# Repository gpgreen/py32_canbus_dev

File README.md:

# py32_canbus_dev

KiCad design for a ARM Cortex-M0+ CAN bus development board with a
MCP2518 CAN FD controller. The mcu part is a Puya PY032F030K18T6. This
can run at a maximum of 48 MHz, and has 8 kbyte SRAM and 64 kbyte
Flash. A USB B mini connector provides 5V power and interfaces with a
FTDI device wired as a Serial Comm to the development board. There is
an onboard LDO that provides 500mA of power at 3.3V. An LED is
connected to 1 of the GPIO pins. All available GPIO pins are routed to
the 2 18pin headers.

The board must be programmed with a debugger, ie at this time it
cannot be programmed over the usb.

## Changes

- Rev A
  Original

## Firmware

Example firmware that blinks the LED. This firmware
uses the HAL provided by Puya and is in C.

https://github.com/gpgreen/py32-dev-blink

## Boot configuration

A boot configuration must be selected for the development board to
operate. If a program has been flashed then booting from main flash
should be selected for that program to run.

To boot from main flash [0x0800_0000] Connect J2-4 to J2-5 (or) solder
  JP5-1 to center post

To boot from System mem [0x1FFF_0000], or Embedded SRAM [0x2000_0000]
  Connect J2-4 to J2-3 (or) solder JP6-3 to center post

There is an embedded boot loader, programmed during mcu chip
production, in the system memory block. See the reference manual
3.6.2.

## PIN JUMPER SIGNAL ASSIGNMENT
```
                     USB-B
                    +-----+
            +--------------------+
            |J3     |     |    J2|
        VDD-|1      +-----+     1|-GND
        GND-|2                  2|-GND
       +3.3-|3                  3|-+3.3
[RESET] PF2-|4                  4|-PF4 [BOOT0_PRE]
[SWCLK]PA14-|5                  5|-GND
[SWDIO]PA13-|6                  6|-GND
        GND-|7       RST        7|-GND
        PF3-|8       +-+        8|-PB7 [USB RX]
        PA0-|9       |O|        9|-PB6 [USB TX]
  [SCK] PA1-|10      +-+       10|-PB5
 [MOSI] PA2-|11                11|-PB4
        PA3-|12                12|-PB3
  [NSS] PA4-|13                13|-PA15
[CAN I] PA5-|14                14|-PA12 [USER LED - GREEN]
 [MISO] PA6-|15                15|-PA11
        PA7-|16                16|-PA10
        PB0-|17                17|-PA9
        PB1-|18    +------+    18|-PA8
            |     1| o  o |2     |
            +--------------------+
                     H  L
                     CAN
```
## Links
- [Puya PY32 Series](https://www.puyasemi.com/cpzx3/info_271_aid_247_kid_246.html)
- [Software template for PY32 Series by Jay Carlson](https://github.com/jaydcarlson/py32-template)
- [Fork of template for these boards](https://github.com/gpgreen/py32-dev-blink)
- [Firmware library for py32f030](https://www.puyasemi.com/download_path/%E5%BA%93%E5%87%BD%E6%95%B0%E4%B8%8E%E4%BE%8B%E7%A8%8B/MCU/PY32F0xx_Firmware_V1.4.1.zip)

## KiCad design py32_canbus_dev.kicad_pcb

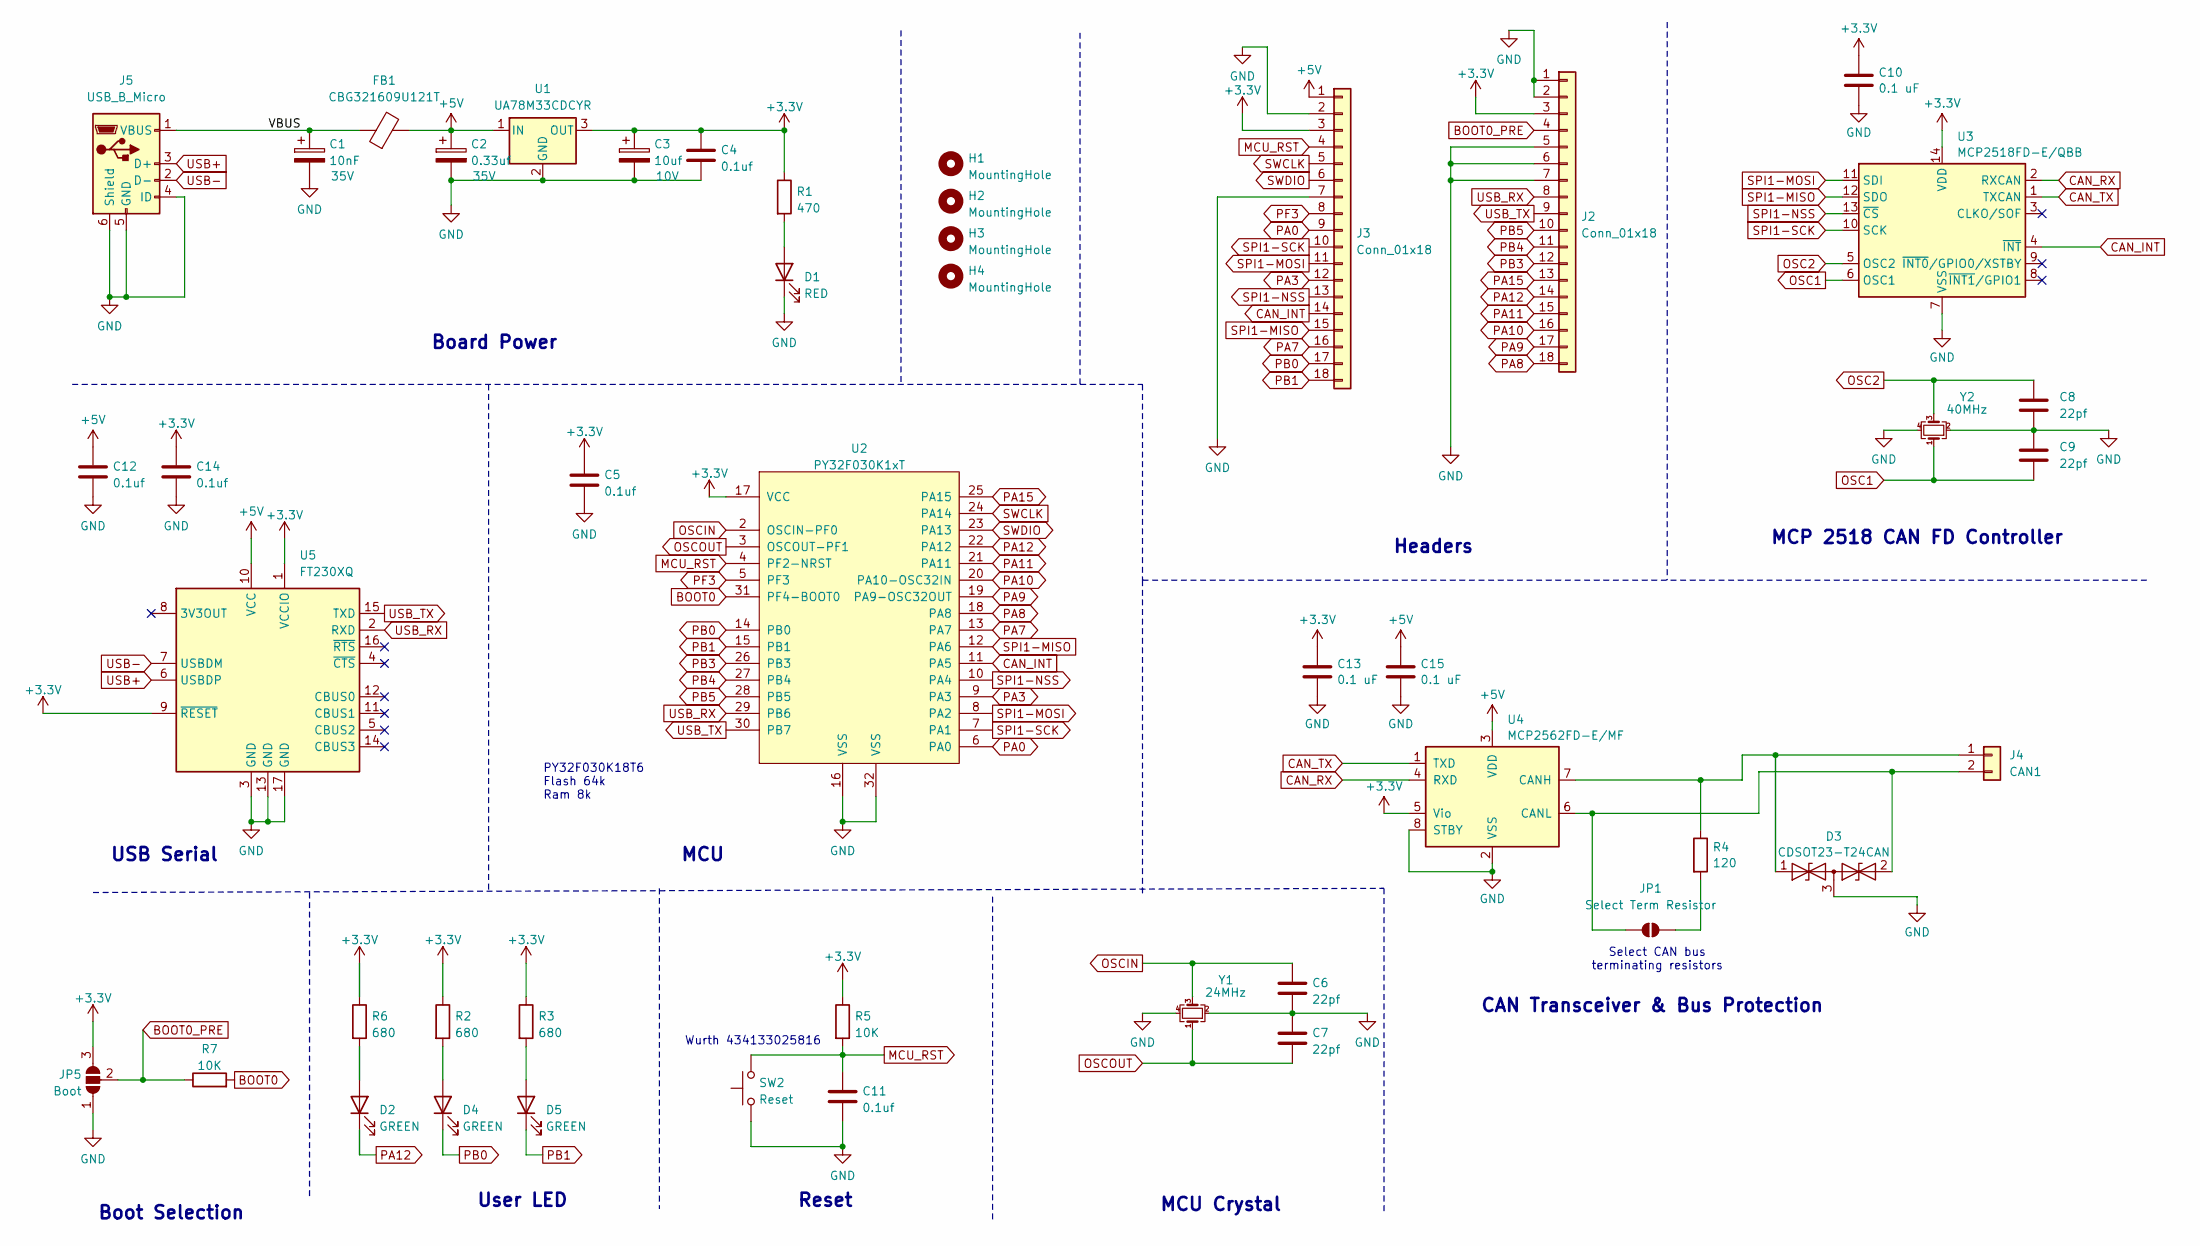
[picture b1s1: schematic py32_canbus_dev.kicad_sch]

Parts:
C1: 10nF; CP_EIA-3216-18_Kemet-A_Pad1.58x1.35mm_HandSolder; Voltage 35V
C2: 0.33uf; CP_EIA-3216-18_Kemet-A_Pad1.58x1.35mm_HandSolder; Voltage 35V
C3: 10uf; CP_EIA-3216-18_Kemet-A_Pad1.58x1.35mm_HandSolder; Voltage 10V
C4, C5, C11, C12, C14: 0.1uf; C_0603_1608Metric
C6, C7, C8, C9: 22pf; C_0603_1608Metric
C10, C13, C15: 0.1 uF; C_0603_1608Metric
D1: RED; D_0603_1608Metric
D2, D4, D5: GREEN; D_0603_1608Metric
D3: CDSOT23-T24CAN; SOT-23
FB1: CBG321609U121T; L_1206_3216Metric
H1, H2, H3, H4: MountingHole; MountingHole_3.2mm_M3
J2, J3: Conn_01x18; PinHeader_1x18_P2.54mm_Vertical
J4: CAN1; JST_EH_B2B-EH-A_1x02_P2.50mm_Vertical
J5: USB_B_Micro; USB_Micro-B_Amphenol_10103594-0001LF_Horizontal
JP1: Select Term Resistor; SolderJumper-2_P1.3mm_Open_Pad1.0x1.5mm
JP5: Boot; SolderJumper-3_P1.3mm_Open_Pad1.0x1.5mm_NumberLabels
R1: 470; R_0603_1608Metric
R2, R3, R6: 680; R_0603_1608Metric
R4: 120; R_1206_3216Metric
R5, R7: 10K; R_0603_1608Metric
SW2: Reset; SW_Push_1P1T_NO_Vertical_Wuerth_434133025816
U1: UA78M33CDCYR; SOT-223-3_TabPin2
U2: PY32F030K1xT; LQFP-32_7x7mm_P0.8mm
U3: MCP2518FD-E/QBB; DFN-14-1EP_3x4.5mm_P0.65mm_EP1.65x4.25mm
U4: MCP2562FD-E/MF; MICROCHIP-DFN-3x3x0.9mm-8P
U5: FT230XQ; QFN-16-1EP_4x4mm_P0.65mm_EP2.1x2.1mm
Y1: 24MHz; Crystal_SMD_TXC_7M-4Pin_3.2x2.5mm
Y2: 40MHz; Crystal_SMD_TXC_7M-4Pin_3.2x2.5mm

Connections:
+3.3V: C3.1, C4.1, C5.1, C10.1, C13.1, C14.1, J2.3, J3.3, JP5.3 (B), R1.1, R2.1, R3.1, R5.1, R6.1, U1.3 (OUT), U2.17 (VCC), U3.14 (VDD), U4.5 (Vio), U5.1 (VCCIO), U5.9 (~RESET)
+5V: C2.1, C12.1, C15.1, FB1.2, J3.1, U1.1 (IN), U4.3 (VDD), U5.10 (VCC)
/VBUS: C1.1, FB1.1, J5.1 (VBUS)
BOOT0: R7.2, U2.31 (PF4-BOOT0)
BOOT0_PRE: J2.4, JP5.2 (C), R7.1
CAN_INT: J3.14, U2.11 (PA5), U3.4 (~INT)
CAN_RX: U3.2 (RXCAN), U4.4 (RXD)
CAN_TX: U3.1 (TXCAN), U4.1 (TXD)
GND: C1.2, C2.2, C3.2, C4.2, C5.2, C6.2, C7.1, C8.2, C9.2, C10.2, C11.2, C12.2, C13.2, C14.2, C15.2, D1.1 (K), D3.3 (common), J2.1, J2.2, J2.5, J2.6, J2.7, J3.2, J3.7, J5.4 (ID), J5.5 (GND), J5.6 (Shield), JP5.1 (A), SW2.1, U1.2 (GND), U2.16 (VSS), U2.32 (VSS), U3.7 (VSS), U3.15 (VSS), U4.2 (VSS), U4.8 (STBY), U5.3 (GND), U5.13 (GND), U5.17 (GND), Y1.2, Y1.4, Y2.2, Y2.4
MCU_RST: C11.1, J3.4, R5.2, SW2.2, U2.4 (PF2-NRST)
unnamed: D1.2 (A), R1.2
unnamed: D2.2 (A), R6.2
unnamed: D3.1 (A1), J4.1, R4.1, U4.7 (CANH)
unnamed: D3.2 (A2), J4.2, JP1.1 (A), U4.6 (CANL)
unnamed: D4.2 (A), R2.2
unnamed: D5.2 (A), R3.2
unnamed: JP1.2 (B), R4.2
OSC1: C9.1, U3.6 (OSC1), Y2.1
OSC2: C8.1, U3.5 (OSC2), Y2.3
OSCIN: C6.1, U2.2 (OSCIN-PF0), Y1.3
OSCOUT: C7.2, U2.3 (OSCOUT-PF1), Y1.1
PA0: J3.9, U2.6 (PA0)
PA3: J3.12, U2.9 (PA3)
PA7: J3.16, U2.13 (PA7)
PA8: J2.18, U2.18 (PA8)
PA9: J2.17, U2.19 (PA9-OSC32OUT)
PA10: J2.16, U2.20 (PA10-OSC32IN)
PA11: J2.15, U2.21 (PA11)
PA12: D2.1 (K), J2.14, U2.22 (PA12)
PA15: J2.13, U2.25 (PA15)
PB0: D4.1 (K), J3.17, U2.14 (PB0)
PB1: D5.1 (K), J3.18, U2.15 (PB1)
PB3: J2.12, U2.26 (PB3)
PB4: J2.11, U2.27 (PB4)
PB5: J2.10, U2.28 (PB5)
PF3: J3.8, U2.5 (PF3)
SPI1-MISO: J3.15, U2.12 (PA6), U3.12 (SDO)
SPI1-MOSI: J3.11, U2.8 (PA2), U3.11 (SDI)
SPI1-NSS: J3.13, U2.10 (PA4), U3.13 (~CS)
SPI1-SCK: J3.10, U2.7 (PA1), U3.10 (SCK)
SWCLK: J3.5, U2.24 (PA14)
SWDIO: J3.6, U2.23 (PA13)
USB+: J5.3 (D+), U5.6 (USBDP)
USB-: J5.2 (D-), U5.7 (USBDM)
USB_RX: J2.8, U2.29 (PB6), U5.2 (RXD)
USB_TX: J2.9, U2.30 (PB7), U5.15 (TXD)

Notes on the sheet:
Select CAN bus terminating resistors
Headers
Boot Selection
MCU Crystal
Reset
MCP 2518 CAN FD Controller
MCU
USB Serial
Wurth 434133025816
CAN Transceiver & Bus Protection
PY32F030K18T6 Flash 64k Ram 8k
Board Power
User LED

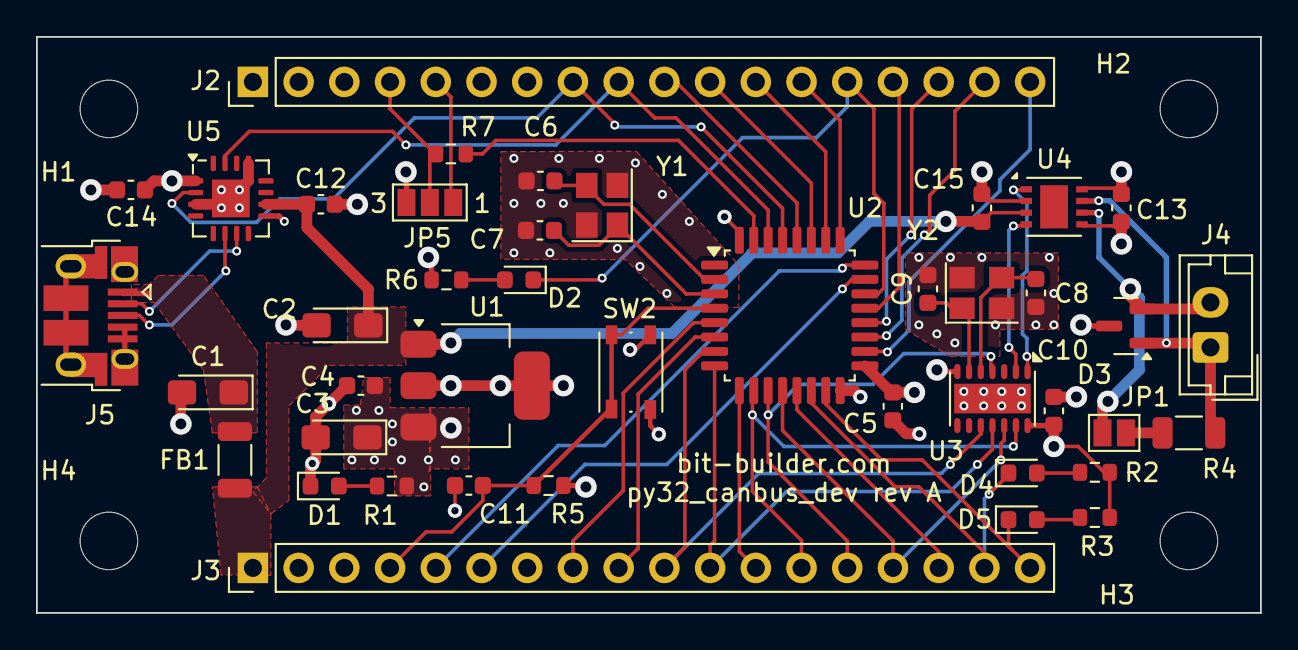
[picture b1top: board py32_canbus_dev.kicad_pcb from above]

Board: 4 copper layers, 68.0 x 32.0 mm, 46 parts (0 on the bottom side), 46 nets.

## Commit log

2024-09-29 Completed schematic and pcb check
2024-09-29 Removed VDD
    Adding LCSC part numbers to BOM
2024-10-06 Showed new pin labels
2024-10-08 Fixed usb tx and rx
2024-12-11 Upped hole diameter, added 2 leds
